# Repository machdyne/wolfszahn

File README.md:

# Wolfszahn Adapter

This is a straight-through 6P 2.54mm SIP to 6P spring socket adapter for [Zwölf](https://github.com/machdyne/zwolf) modules.

This repo contains the schematics, PCB layout, BOM and 3D-printable socket housing for the Wolfszahn adapter.

Find more information on the [Wolfszahn product page](https://machdyne.com/product/zwolf-wolfszahn-adapter/).

## License

The contents of this repo are released under the [Lone Dynamics Open License](LICENSE.md).

Note: You can use these designs for commercial purposes but we ask that instead of producing exact clones, that you either replace our trademarks and logos with your own or add your own next to ours.

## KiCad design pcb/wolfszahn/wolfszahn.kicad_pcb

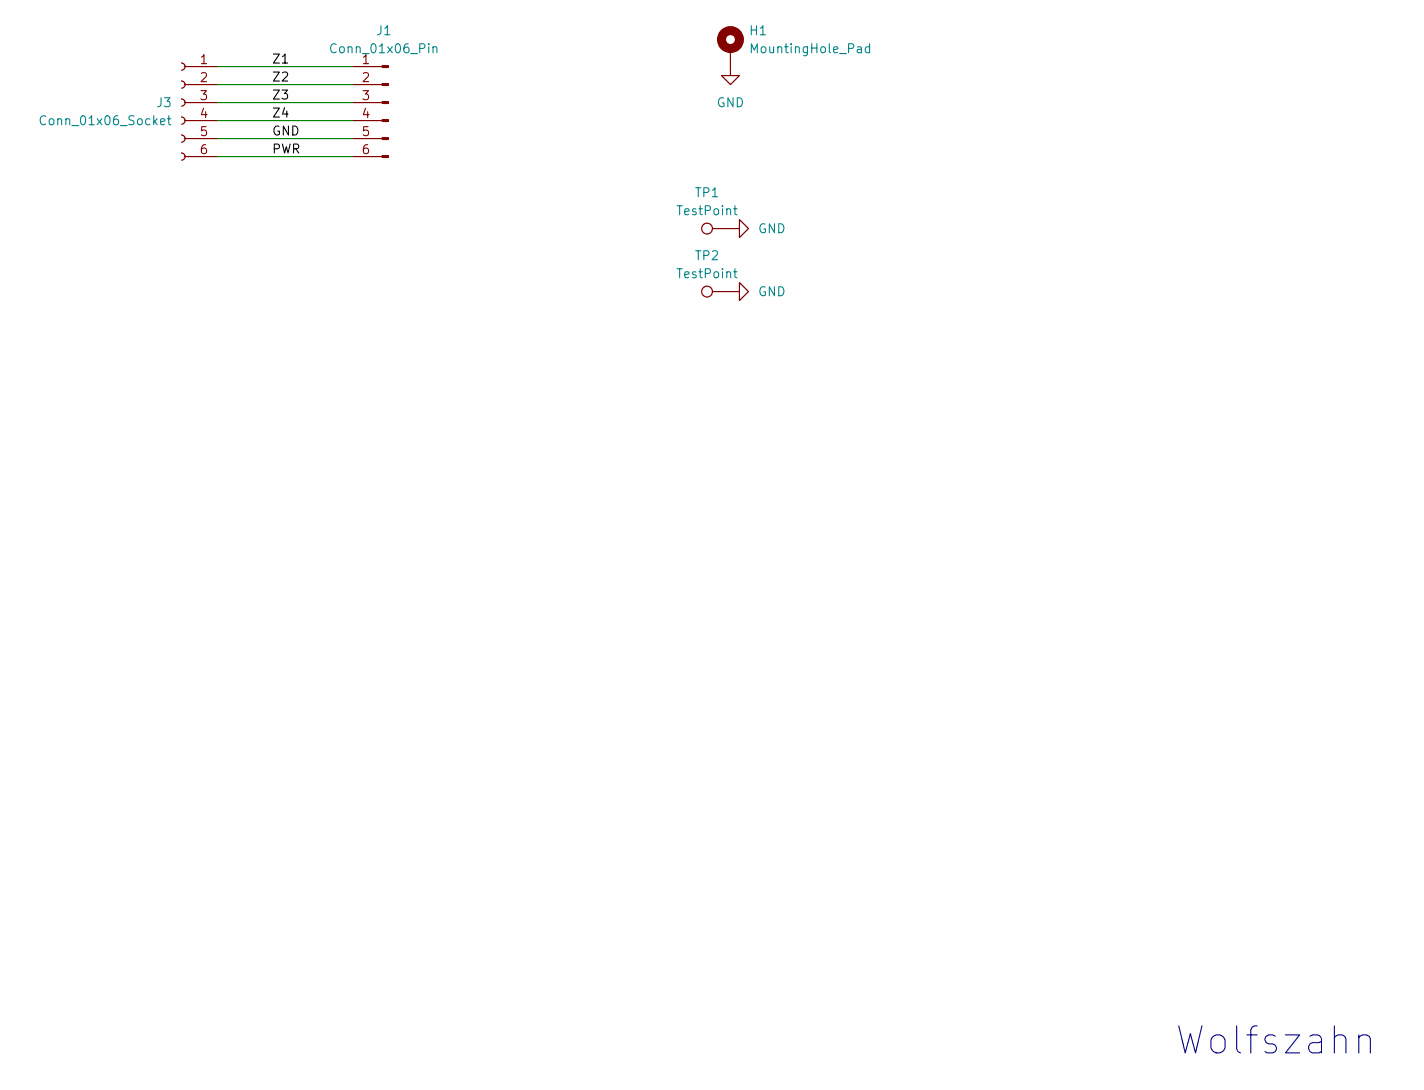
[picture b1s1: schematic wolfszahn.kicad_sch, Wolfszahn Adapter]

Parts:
H1: MountingHole_Pad; MountingHole_2.7mm_M2.5_DIN965_Pad_TopOnly
J1: Conn_01x06_Pin; PinHeader_1x06_P2.54mm_Horizontal
J3: Conn_01x06_Socket; SPRING-MALE-6P-TIGHTHOLES
TP1, TP2: TestPoint; TestPoint_Pad_1.5x1.5mm

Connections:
/PWR: J1.6, J3.6
/Z1: J1.1, J3.1
/Z2: J1.2, J3.2
/Z3: J1.3, J3.3
/Z4: J1.4, J3.4
GND: H1.1, J1.5, J3.5, TP1.1, TP2.1

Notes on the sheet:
Wolfszahn

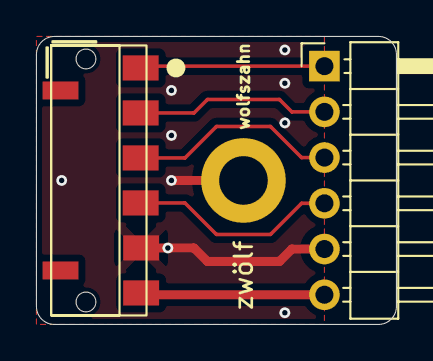
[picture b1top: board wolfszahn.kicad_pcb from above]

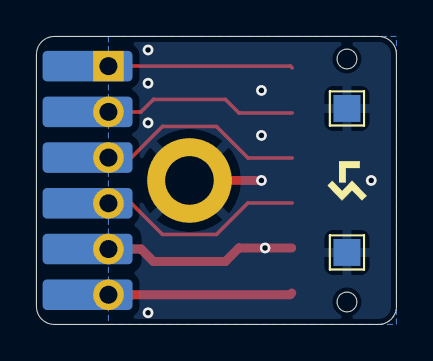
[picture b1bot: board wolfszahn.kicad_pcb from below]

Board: 2 copper layers, 20.0 x 16.0 mm, 5 parts (2 on the bottom side), 6 nets.

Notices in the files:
pcb/wolfszahn/wolfszahn.kicad_sch:
Copyright © 2024 Lone Dynamics Corporation
